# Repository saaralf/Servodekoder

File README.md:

# Servodekoder (OpenSX)

Dieses Repository enthält:
- Hardware
  - `hardware/Servo.sch` / `hardware/Servo.brd` (Servo-Aufsatz mit PCA9685)
  - `hardware/SXV0300_Servo.sch` / `hardware/SXV0300_Servo.brd` (Basisplatine v300 Servo)
- Software
  - `software/ServoTest/ServoTest.ino` (Arduino-Testsketch für PCA9685)
  - `software/SX-Servo-Aufsatz/` (PlatformIO-Projekt, Arbeitsstand)

## Annahmen / Pinning
- PCA9685 Adresse fest: `0x40` (A0..A5 auf GND)
- I2C vom Pro Mini:
  - A4 = SDA
  - A5 = SCL
- Basisplatine: A5_RX-Jumper muss auf **A5** stehen (nicht RX)

## Versorgungskonzept
- Externe Servo-Versorgung wird über die Basisplatine eingespeist.
- Servo-Aufsatz führt +5V über MOSFET-Schutzpfad.
- GND zwischen Logik und Servo muss gemeinsam sein.

## Bilder unserer Platinen
- Aufsatz:
  
- Basisplatine:

## Test
- Sketch hochladen: `software/ServoTest/ServoTest.ino`
- Serielle Konsole 115200 öffnen
- Befehle im Sketch: `h`, `s`, `a <winkel>`, `c <kanal> <winkel>`, `d`

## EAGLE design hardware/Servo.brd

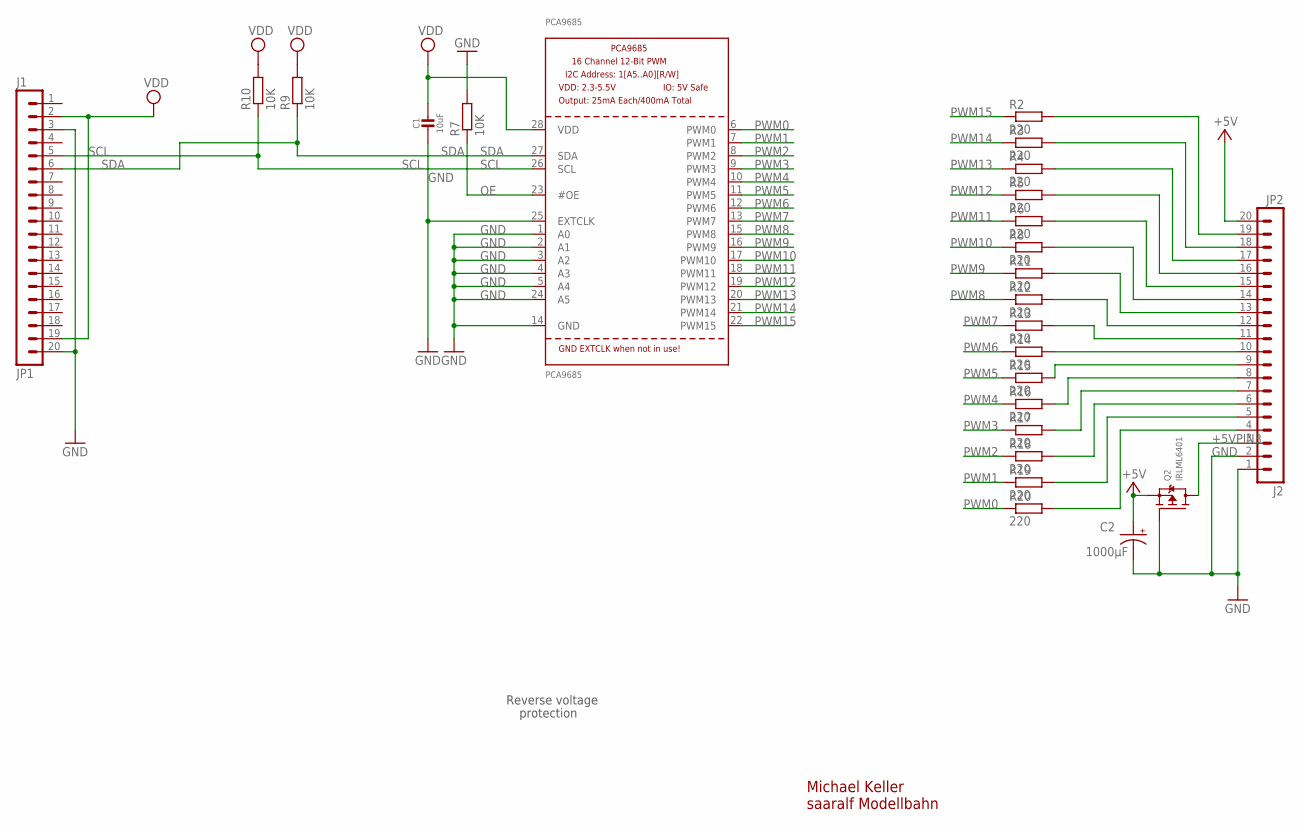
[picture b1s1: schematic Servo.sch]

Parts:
C1: 10uF; 0805-NO
C2: 1000µF; E3,5-8
JP1: J1; MA20-1
JP2: J2; MA20-1
PCA9685: PCA9685; TSSOP28
Q2: IRLML6401; SOT23-WIDE
R2, R3, R4, R5, R6, R8, R11, R12, R13, R14, R15, R16, R17, R18, R19, R20: 220; M0805
R7, R9, R10: 10K; M0805

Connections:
+5V: C2.+, JP2.20, Q2.2 (S)
+5VPIN3: JP2.3, Q2.3 (D)
GND: C1.2, C2.-, JP1.3, JP1.20, JP2.1, JP2.2, PCA9685.1 (A0), PCA9685.2 (A1), PCA9685.3 (A2), PCA9685.4 (A3), PCA9685.5 (A4), PCA9685.14 (GND), PCA9685.24 (A5), PCA9685.25 (EXTCLK), Q2.1 (G), R7.2
unnamed: JP2.17, R4.2
unnamed: JP2.11, R13.2
unnamed: JP2.10, R14.2
unnamed: JP2.9, R15.2
unnamed: JP2.7, R17.2
unnamed: JP2.6, R18.2
unnamed: JP2.5, R19.2
unnamed: JP2.4, R20.2
unnamed: JP2.15, R6.2
unnamed: JP2.14, R8.2
unnamed: JP2.18, R3.2
unnamed: JP2.13, R11.2
unnamed: JP2.19, R2.2
unnamed: JP2.8, R16.2
unnamed: JP2.16, R5.2
unnamed: JP2.12, R12.2
OE: PCA9685.23 (#OE), R7.1
PWM0: PCA9685.6 (PWM0), R20.1
PWM1: PCA9685.7 (PWM1), R19.1
PWM2: PCA9685.8 (PWM2), R18.1
PWM3: PCA9685.9 (PWM3), R17.1
PWM4: PCA9685.10 (PWM4), R16.1
PWM5: PCA9685.11 (PWM5), R15.1
PWM6: PCA9685.12 (PWM6), R14.1
PWM7: PCA9685.13 (PWM7), R13.1
PWM8: PCA9685.15 (PWM8), R12.1
PWM9: PCA9685.16 (PWM9), R11.1
PWM10: PCA9685.17 (PWM10), R8.1
PWM11: PCA9685.18 (PWM11), R6.1
PWM12: PCA9685.19 (PWM12), R5.1
PWM13: PCA9685.20 (PWM13), R4.1
PWM14: PCA9685.21 (PWM14), R3.1
PWM15: PCA9685.22 (PWM15), R2.1
SCL: JP1.5, PCA9685.26 (SCL), R10.1
SDA: JP1.6, PCA9685.27 (SDA), R9.1
VDD: C1.1, JP1.2, JP1.19, PCA9685.28 (VDD), R9.2, R10.2

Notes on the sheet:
Michael Keller saaralf Modellbahn
Reverse voltage
protection

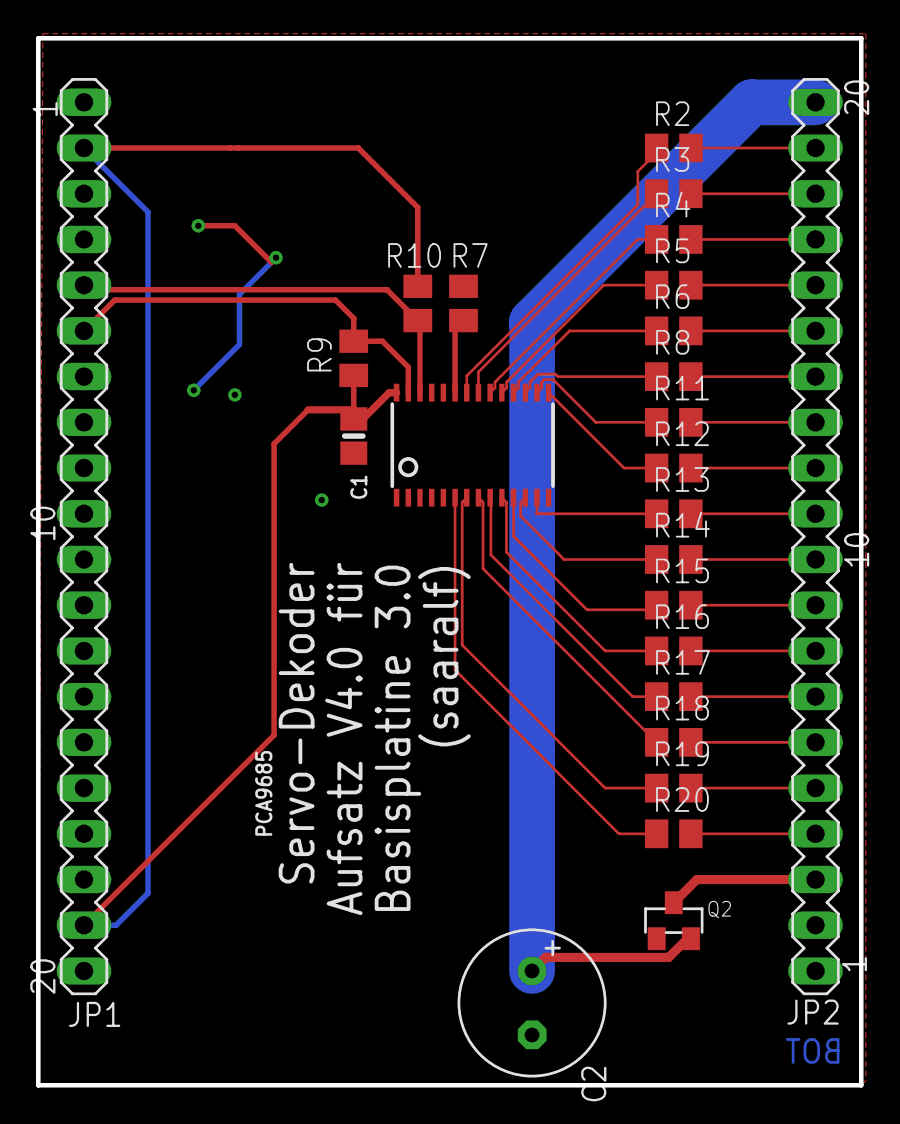
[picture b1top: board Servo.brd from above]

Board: 2 copper layers, 45.7 x 58.2 mm, 25 parts (0 on the bottom side), 39 nets.

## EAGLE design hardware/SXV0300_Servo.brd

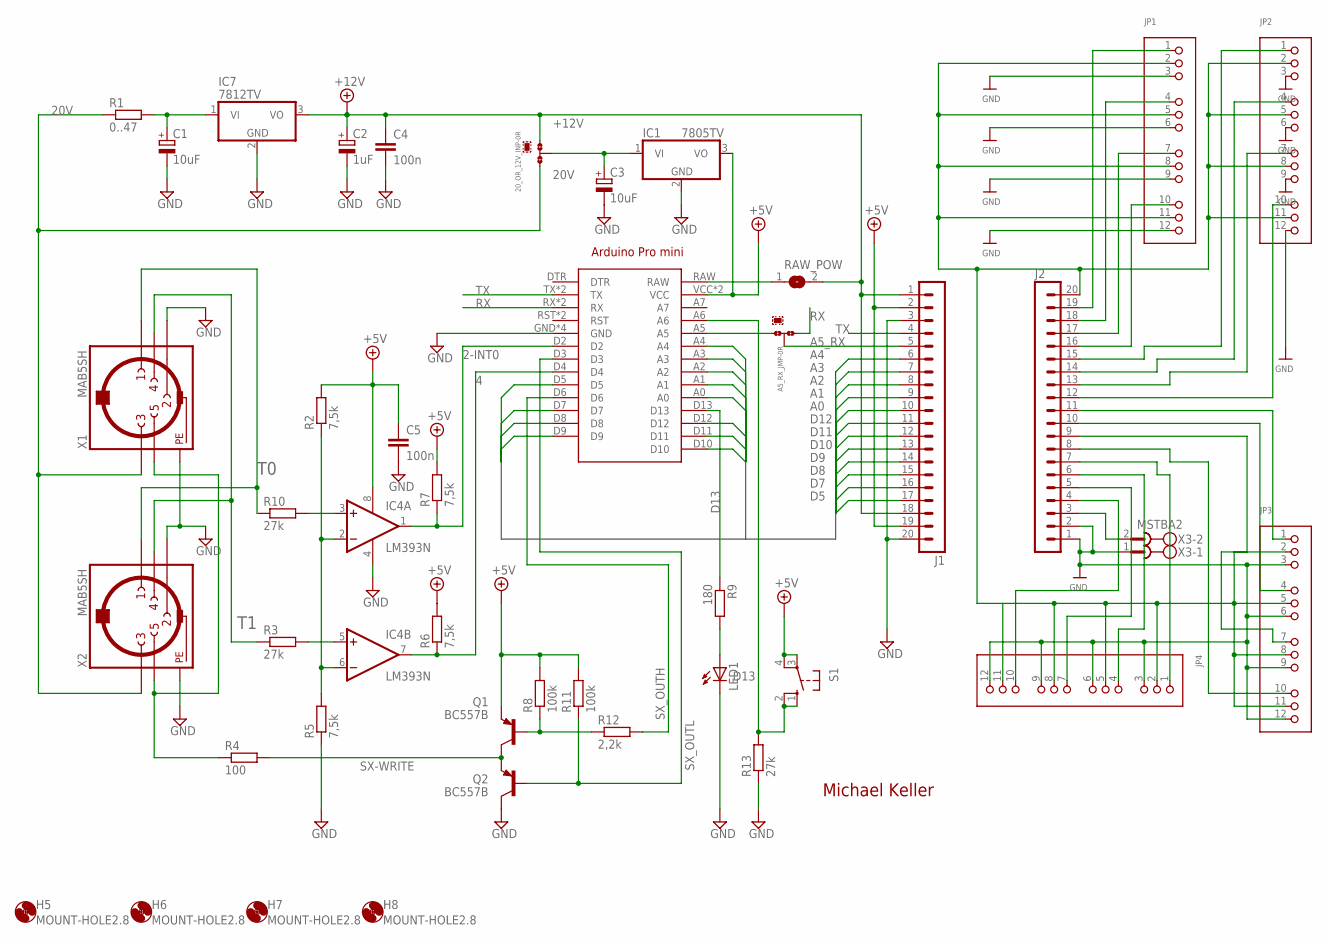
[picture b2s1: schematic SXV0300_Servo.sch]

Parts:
20_OR_12V_INP: 0R-JUMPA; A0R-JMP
A5_RX_JMP: 0R-JUMPB; B0R-JMP
ARDUINO1: ARDUINO_PRO_MINI
C1: 10uF; E2,5-7
C2: 1uF; E2,5-7
C3: 10uF; SMC_C
C4, C5: 100n; C050-025X075
H5, H6, H7, H8: MOUNT-HOLE2.8; 2,8
IC1: 7805TV; TO220V
IC4: LM393N; DIL08
IC7: 7812TV; TO220V
J1, J2: MA20-1
JP1, JP2, JP3, JP4: HEADER-3X04; 3X04
LED1: LED3MM
Q1, Q2: BC557B; TO92-EBC
R1: 0..47; 0207/12
R2, R5, R6, R7: 7,5k; 0207/10
R3, R10, R13: 27k; 0207/10
R4: 100; 0207/10
R8, R11: 100k; 0207/10
R9: 180; 0207/2V
R12: 2,2k; 0207/10
RAW_POW: SJ
S1: 10-XX; B3F-10XX
X1, X2: MAB5SH
X3: MSTBA2

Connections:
2-INT0: ARDUINO1.D2, IC4.1 (OUT), R7.1
4: ARDUINO1.D4, IC4.7 (OUT), R6.1
20V: 20_OR_12V_INP.3, R1.1, X1.3, X2.3
+5V: ARDUINO1.VCC, ARDUINO1.VCC@1 (VCC), C5.1, IC1.3 (VO), IC4.8 (V+), J1.2, J1.19, Q1.E, R2.2, R6.2, R7.2, R8.2, R11.2, S1.3, S1.4 (P1)
+12V: 20_OR_12V_INP.1, C2.+, C4.1, IC7.3 (VO), J1.1, J1.18, RAW_POW.2
A0: ARDUINO1.A0, J1.10
A1: ARDUINO1.A1, J1.9
A2: ARDUINO1.A2, J1.8
A3: ARDUINO1.A3, J1.7
A4: ARDUINO1.A4, J1.6
A5: A5_RX_JMP.3, ARDUINO1.A5
A5_RX: A5_RX_JMP.2, J1.5
D5: ARDUINO1.D5, J1.17
D7: ARDUINO1.D7, J1.16
D8: ARDUINO1.D8, J1.15
D9: ARDUINO1.D9, J1.14
D10: ARDUINO1.D10, J1.13
D11: ARDUINO1.D11, J1.12
D12: ARDUINO1.D12, J1.11
D13: ARDUINO1.D13, R9.1
GND: ARDUINO1.GND, ARDUINO1.GND@1 (GND), ARDUINO1.GND@2 (GND), ARDUINO1.GND@3 (GND), C1.-, C2.-, C3.-, C4.2, C5.2, IC1.2 (GND), IC4.4 (V-), IC7.2 (GND), J1.3, J1.20, J2.1, J2.2, JP1.3, JP1.6, JP1.9, JP1.12, JP2.3, JP2.6, JP2.9, JP2.12, JP3.3, JP3.6, JP3.9, JP3.12, JP4.3, JP4.6, JP4.9, JP4.12, LED1.K (C), Q2.C, R5.1, R13.1, X1.2, X1.PE, X1.PE@ (PE), X1.PE@1 (PE), X1.PE@2 (PE), X2.2, X2.PE, X2.PE@ (PE), X2.PE@1 (PE), X2.PE@2 (PE), X3.1
unnamed: LED1.A, R9.2
unnamed: C1.+, IC7.1 (VI), R1.2
unnamed: R4.1, X1.5, X2.5
unnamed: IC4.3 (+IN), R10.2
unnamed: IC4.5 (+IN), R3.2
unnamed: J2.20, JP1.2, JP1.5, JP1.8, JP1.11, JP2.2, JP2.5, JP2.8, JP2.11, JP3.2, JP3.5, JP3.8, JP3.11, JP4.2, JP4.5, JP4.8, JP4.11
unnamed: IC4.2 (-IN), IC4.6 (-IN), R2.1, R5.2
unnamed: J2.3, X3.2
unnamed: J2.4, JP4.10
unnamed: J2.5, JP4.7
unnamed: J2.6, JP4.4
unnamed: J2.7, JP4.1
unnamed: J2.8, JP3.10
unnamed: J2.9, JP3.7
unnamed: J2.10, JP3.4
unnamed: J2.11, JP3.1
unnamed: J2.12, JP2.10
unnamed: J2.13, JP2.7
unnamed: J2.14, JP2.4
unnamed: J2.15, JP2.1
unnamed: J2.16, JP1.10
unnamed: J2.17, JP1.7
unnamed: J2.18, JP1.4
unnamed: J2.19, JP1.1
unnamed: ARDUINO1.A6, R13.2, S1.1 (S), S1.2 (S1)
unnamed: Q1.B, R8.1, R12.1
unnamed: ARDUINO1.RAW, RAW_POW.1
unnamed: 20_OR_12V_INP.2, C3.+, IC1.1 (VI)
RX: A5_RX_JMP.1, ARDUINO1.RX, ARDUINO1.RX@1 (RX)
SX-WRITE: Q1.C, Q2.E, R4.2
SX_OUTH: ARDUINO1.D6, R12.2
SX_OUTL: ARDUINO1.D3, Q2.B, R11.1
T0: R10.1, X1.1, X2.1
T1: R3.1, X1.4, X2.4
TX: ARDUINO1.TX, ARDUINO1.TX@1 (TX), J1.4

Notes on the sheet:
Michael Keller

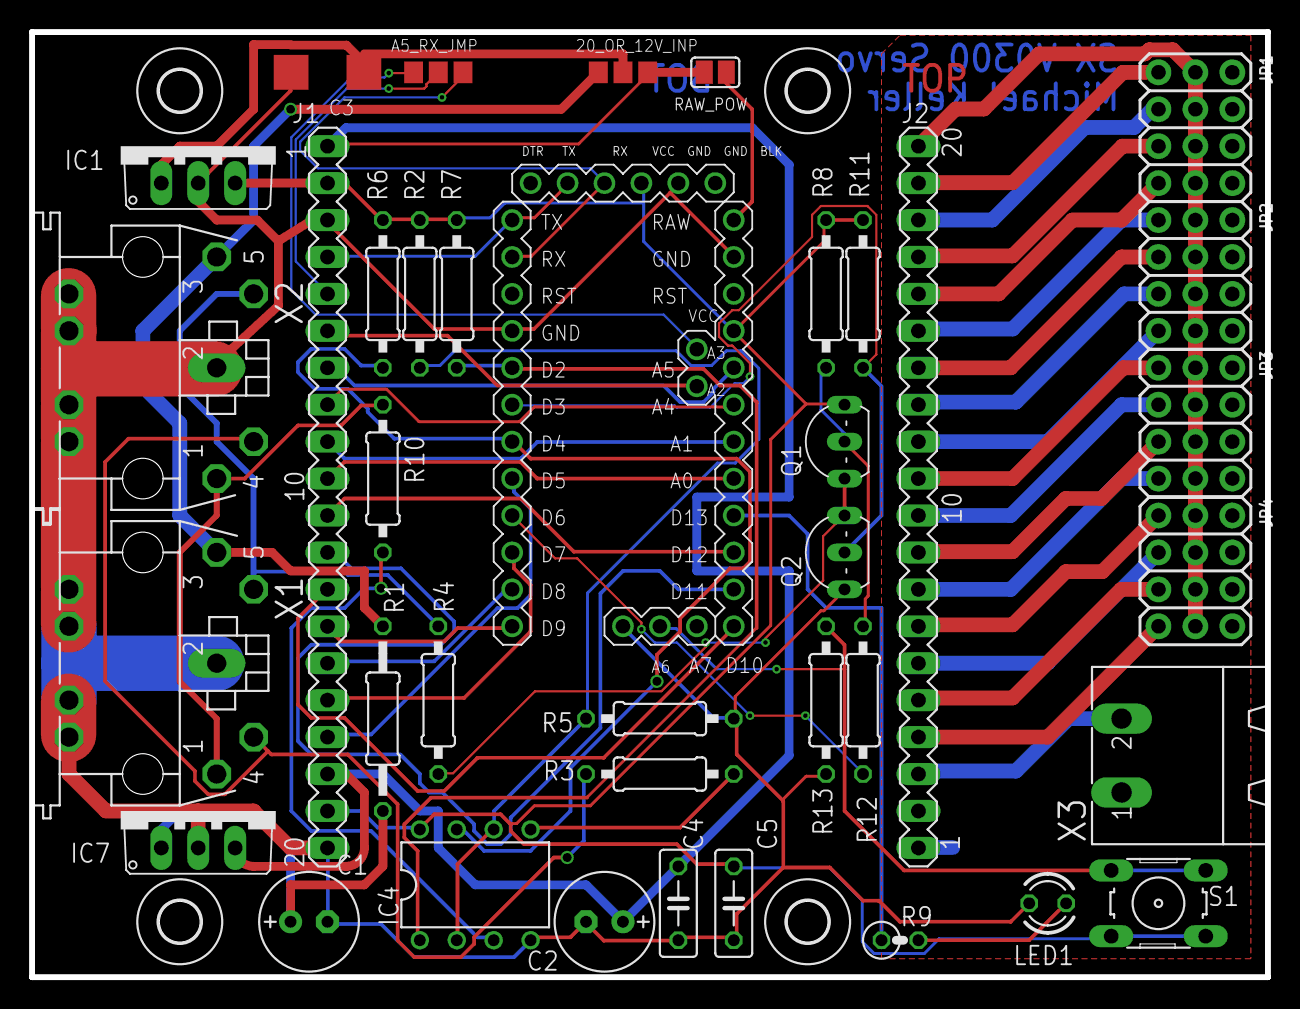
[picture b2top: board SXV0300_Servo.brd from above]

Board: 2 copper layers, 85.0 x 65.0 mm, 42 parts (0 on the bottom side), 56 nets.

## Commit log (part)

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2026-04-14 Initial commit: Servo decoder hardware + test sketch
2026-04-14 Add wiring docs, short description with images, and gitignore
2026-04-14 Add new board photos and embed them in README and short description
2026-04-14 Add BlinkTest sketch and PlatformIO PCA9685 library dependencies
2026-04-14 Add Serial Monitor heartbeat test and set monitor speed to 115200
2026-04-15 Extend ServoTest with dedicated channel-0 test command
2026-04-16 ServoTest: start at 0° and add +/- serial control for servo 0
2026-04-16 ServoTest: add signed mode for channel 0 (-90..0..+90 around center)
2026-04-16 SX-Servo-Aufsatz main.cpp: signed servo-0 control (-90..0..+90)
2026-04-16 Add EEPROM-backed servo soft-limit calibration workflow (no switch feedback)
2026-04-16 Improve serial command robustness and explicit feedback for l/r limit commands
2026-04-16 Add turnout commands (gerade/abzweig) and saveable diverging side orientation
2026-04-16 Allow finer +/- calibration and default travel up to +/-40 with clear softlimit hint
2026-04-16 Show turnout state (GERADE/ABZWEIG/MITTE/ZWISCHEN) in status output
2026-04-16 Include servo status output in 's' I2C scan command
2026-04-16 On boot: detect EEPROM config, report source, and always move servo to center first
2026-04-17 Add backup copy of current SX-Servo-Aufsatz main.cpp test program
2026-04-17 Add SX30-based 16-servo turnout decoder sketch with programming mode and EEPROM config
2026-04-17 Restructure SX30-ServoDecoder to PlatformIO standard src/main.cpp layout
2026-04-17 Vendor SX30 library into project lib folder and remove external lib path dependency
2026-04-17 Support single SX address mode (8 servos) with disabled-address handling
2026-05-02 Wiederstände als 0803
2026-05-03 SX-Servo-Aufsatz: SX30 programmer mode, EEPROM config, servo test channels and relax
2026-05-03 Add remaining local files and archive SX monitor Qt source
2026-05-04 SXServo: add TODO for QT prog-button feedback, D13 setup-mode indicator
2026-05-04 sx-monitor-qt: add build and requirements documentation
2026-05-04 sx-monitor-qt-v2: remove build artifacts and ignore build directory
2026-05-04 sx-monitor-qt-v2: add Servo-Bildansicht tab with 16 tiles (2x8)
2026-05-05 sx-monitor-qt-v2: replace ASCII arm with painted servo arm widget
2026-05-05 sx-monitor-qt-v2: style servo tile closer to KY66 (blue body, white long horn)
2026-05-05 sx-monitor-qt-v2: render servo upright (vertical body orientation)
2026-05-05 sx-monitor-qt-v2: match widget bg to app theme and restore visible arm overlay
2026-05-05 sx-monitor-qt-v2: always draw visible upright servo body behind rotating arm
2026-05-05 sx-monitor-qt-v2: enlarge and emphasize symmetric long double-sided horn
2026-05-05 sx-monitor-qt-v2: render directly from user-provided body/arm assets
2026-05-05 sx-monitor-qt-v2: fix missing body visibility and clean arm alpha overlay
2026-05-05 sx-monitor-qt-v2: step 1 show upright servo body only
2026-05-05 sx-monitor-qt-v2: remove white body background and use cut body asset
2026-05-05 sx-monitor-qt-v2: integrate new blue servo body image asset
2026-05-05 sx-monitor-qt-v2: align arm rotation to hub via automatic alpha-center offset
2026-05-05 sx-monitor-qt-v2: use user-edited transparent servo body image
2026-05-05 sx-monitor-qt-v2: use user-edited transparent servo arm image
2026-05-05 sx-monitor-qt-v2: adjust arm overlay trim to align with servo hub
2026-05-05 sx-monitor-qt-v2: move arm higher/right and allow arm to extend beyond tile
2026-05-05 sx-monitor-qt-v2: final x-offset tweak for arm-to-hub centering
2026-05-05 sx-monitor-qt-v2: apply final 1px right arm alignment tweak
2026-05-05 sx-monitor-qt-v2: align arm by matching asset hub centers (body hub vs arm hub)
2026-05-05 sx-monitor-qt-v2: enlarge servo image area so full arm stays visible
2026-05-05 sx-monitor-qt-v2: add address/bit mapping header in visual tab and hide send bar on visual page
2026-05-05 sx-monitor-qt-v2: improve visual tile title format for readability
2026-05-05 sx-monitor-qt-v2: restructure visual grid with per-column Servo/Adresse/Bit rows
2026-05-05 sx-monitor-qt-v2: place address 2 controls between first and second servo rows
2026-05-05 sx-monitor-qt-v2: add SX bus selector to visual tab top and sync with sender bus
2026-05-05 sx-monitor-qt-v2: auto-activate visual setup context for move/store actions
2026-05-05 sx-monitor-qt-v2: stop retriggering K10 on every move/store click to prevent re-centering jitter
2026-05-05 sx-monitor-qt-v2: auto-detect SLX852 port via /dev/serial/by-id and preselect on connect
2026-05-05 sx-monitor-qt-v2: do not override manually selected serial port on connect
2026-05-05 sx-monitor-qt-v2: restore robust manual send path via unified sendSX bus-select and 4x write
2026-05-05 sx-monitor-qt-v2: add baud dropdown and fail connect when FE test write fails
2026-05-05 sx-monitor-qt-v2: use 1-based servo index for K11 in visual move/store commands
2026-05-05 sx-monitor-qt-v2: match programmer setup handshake in V2 (K15=1 before K10 pulse)
2026-05-05 sx-monitor-qt-v2: align visual move/store K11 indexing and command path with working programmer logic
2026-05-05 sx-monitor-qt-v2: add visual-tab setup end/abort buttons (K10=3/2) to control D13 state
2026-05-05 SX30-ServoDecoder: allow serial setup commands even during SX-wizard setup mode
2026-05-05 sx-monitor-qt-v2: require user-gated programming request in visual tab (no automatic K10 start)
2026-05-06 sx-monitor-qt-v2: restore V1-proven wizard send path for visual move/store
2026-05-06 sx-monitor-qt-v2: unify programmer and visual wizard communication through shared handlers
2026-05-06 sx-monitor-qt-v2: use 1-based servo id on K11 in shared wizard handlers
2026-05-06 sx-monitor-qt-v2: remove duplicate bus selector in SX senden; use top bus selection only
2026-05-06 sx-monitor-qt-v2: send K15=1 in shared wizard move/store path for stable setup control
2026-05-06 sx-monitor-qt-v2: add explicit debug log for wizard move payload (K1/K2/K11/K12/K13/K15)
2026-05-06 sx-monitor-qt-v2: auto-fallback AddrB to AddrA+1 when AddrB is 0 in wizard commands
2026-05-06 sx-monitor-qt-v2: verify SX interface on connect by requiring post-FE traffic
2026-05-09 SXServo: snapshot main + Qt V2 bus send cleanup and version stamp
2026-05-09 Qt V2: add RX pause mode to isolate TX+telemetry from noisy SX monitor parser
2026-05-09 Qt V2: show dynamic git branch+commit in title and startup log
2026-05-09 Firmware: bump FW_VERSION to 2026-05-09b and codify version-bump rule
2026-05-09 Qt V2: do not abort connect when initial SX stream is quiet; continue with warning
2026-05-09 Qt V2 ACK: increase timeouts, auto-request CFG after store, and treat CFG_END as store verification
2026-05-09 Qt V2: auto-verify move via CFG request and resolve pending move on CFG_END
2026-05-09 Firmware SX wizard: swap move direction mapping for SX path and bump FW to 2026-05-09c
2026-05-09 Firmware SX wizard hardening: setup guard window + post-end ignore window; bump FW to 2026-05-09e; update TODO
2026-05-09 SX wizard session token: add K9 session-id gating in Qt+firmware, invalidate on end, bump FW to 2026-05-09f
2026-05-09 Firmware SX hardening: accept CMD start only with valid session + K15=1 + matching K1 addr; bump FW to 2026-05-09g
2026-05-09 Firmware SX start edge hardening: require stable cmd=0 preamble before cmd=1; bump FW to 2026-05-09h
2026-05-09 Firmware: lock wizard to initial SX servo within session to prevent cross-servo twitch; clear lock on end; bump FW to 2026-05-09j
2026-05-09 Qt telemetry stabilization: throttle auto-CFG on move, block overlapping CFG requests, and require complete CFG import for ACK via CFG
2026-05-09 Git hygiene: ignore legacy Qt build output directory
2026-05-09 Qt V2 UX hardening: disable servo tile inputs while ACK is pending; re-enable on ACK ok/timeout
2026-05-09 Firmware move diagnostics: log relBefore/relAfter for serial+SX moves (including mid); bump FW to 2026-05-09l
2026-05-09 Qt telemetry parser: classify unknown lines as noise and ignore them for wizard state handling
2026-05-09 Qt ACK policy: accept move/store only from real ACK_SETUP_* lines; CFG_END is informational; clarify timeout reason
2026-05-09 Qt split-mode ACK: add optional CFG-fallback mode with explicit ACK:cfg-fallback status for notbetrieb
2026-05-09 Qt UI: add prominent ACK mode banner (STRICT green / NOTBETRIEB CFG-Fallback orange)
2026-05-09 Fix Serial-Wizard gating: bypass SX session-id blocks for move/store and mark serial start as active session
2026-05-09 Qt defaults: make Serial-Wizard recommended default, label SX path experimental, and add quick Serial-Wizard test guide
2026-05-12 Serial-Wizard stabilization: disable auto-CFG after moves and add short inter-command quiet time
2026-05-12 Path separation hardening: block 'SX Senden' while Serial-Wizard setup is active
2026-05-12 Firmware: enforce PROG LED off when track power is ON; close setup/wizard state on track ON; bump FW to 2026-05-09n
2026-05-12 Serial-Wizard UX fixes: prevent repeated START spam, reset setup state on save/abort, and auto-enable/disable setup/SX-send controls
2026-05-12 SX connect UX: show explicit warning dialogs on connect/open failure and display tty device with by-id hint while using by-id internally
2026-05-12 Connect diagnostics: always log failed SX connect attempts and show tty+by-id in error messages
2026-05-18 feat: sxbusd2 full-address live polling at 77ms
2026-05-19 test: add RMX vs SX1 ADR126 comparison tool and report
2026-05-20 chore(systemd): add dual daemon service units for sx and rmx
2026-05-21 wip: checkpoint all local changes
2026-05-21 feat(qt): add SX/RMX backend selector and immediate track refresh on connect
2026-05-22 feat(qt-v3): bootstrap modular dual-connection app for SX+RMX
2026-05-22 feat(qt-v3): add minimal Send Test row (backend/bus/adr/value)
2026-05-22 feat(qt-v3): add Read Test button with READADR request path
2026-05-22 feat(qt-v3): add auto-read button for ADR126/127 on SX and RMX
2026-05-22 feat(qt-v3): add RX filter toggle for ADR126/127
2026-05-22 feat(qt-v3): add clear-log button to test row
2026-05-22 refactor(qt-v3): split test controls into two grouped rows
2026-05-22 feat(qt-v3): add SX and RMX monitor tabs with live address tables
2026-05-22 feat(qt-v3): switch SX/RMX monitor tabs to 0..111 3-column addr/dec/bits layout
2026-05-22 feat(qt-v3): add per-tab bus selector (SX0/SX1, RMX0/RMX1) with cached view
2026-05-22 style(qt-v3): align monitor table visuals exactly with V2 defaults
2026-05-22 ui(qt-v3): size SX/RMX monitor tabs to content height and disable table scrolling
2026-05-22 ui(qt-v3): auto-size main window to full monitor tab content on startup
2026-05-22 feat(qt-v3): add Servo-Bildansicht V2 tab scaffold with 16 servo tiles
2026-05-22 feat(qt-v3): enhance V2 visual servo tab with per-tile actions and dynamic addr/bit mapping
2026-05-22 feat(qt-v3): port V2 ServoArmWidget assets into visual tab tiles
2026-05-22 refactor(qt-v3): align visual servo tab structure closer to original V2 layout
2026-05-24 fix(qt-v3): address QA findings in visual servo tab and daemon connection UI
2026-05-24 fix(qt-v3): show daemon protocol lines and clamp visual servo step increments
2026-05-24 feat(qt-v3): show daemon-connected hardware-pending state in connection panel
2026-05-24 feat(sxbusd2): keep daemon online and auto-probe for SX hardware
2026-05-24 feat(qt-v3): configure daemon USB ports
2026-05-24 style(qt-v3): add RMX central inspired theme
2026-05-24 fix(qt-v3): stabilize connection row label widths
2026-05-24 feat(qt-v3): add SX bit-send dialog from monitor table
2026-05-24 feat(qt-v3): one-click SX bit toggle in monitor
2026-05-24 ui(qt-v3): use real bit buttons in SX monitor
2026-05-24 feat(qt-v3): add SX monitor bit order switch for bit buttons
2026-05-24 fix(qt-v3): skip daemon start/connect when USB port is unconfigured
2026-05-24 refactor: split qt v2/v3 into physical top-level layout and harden v3 logging/usb defaults
2026-06-01 Neue Version V2 des ServoAufsatzes
